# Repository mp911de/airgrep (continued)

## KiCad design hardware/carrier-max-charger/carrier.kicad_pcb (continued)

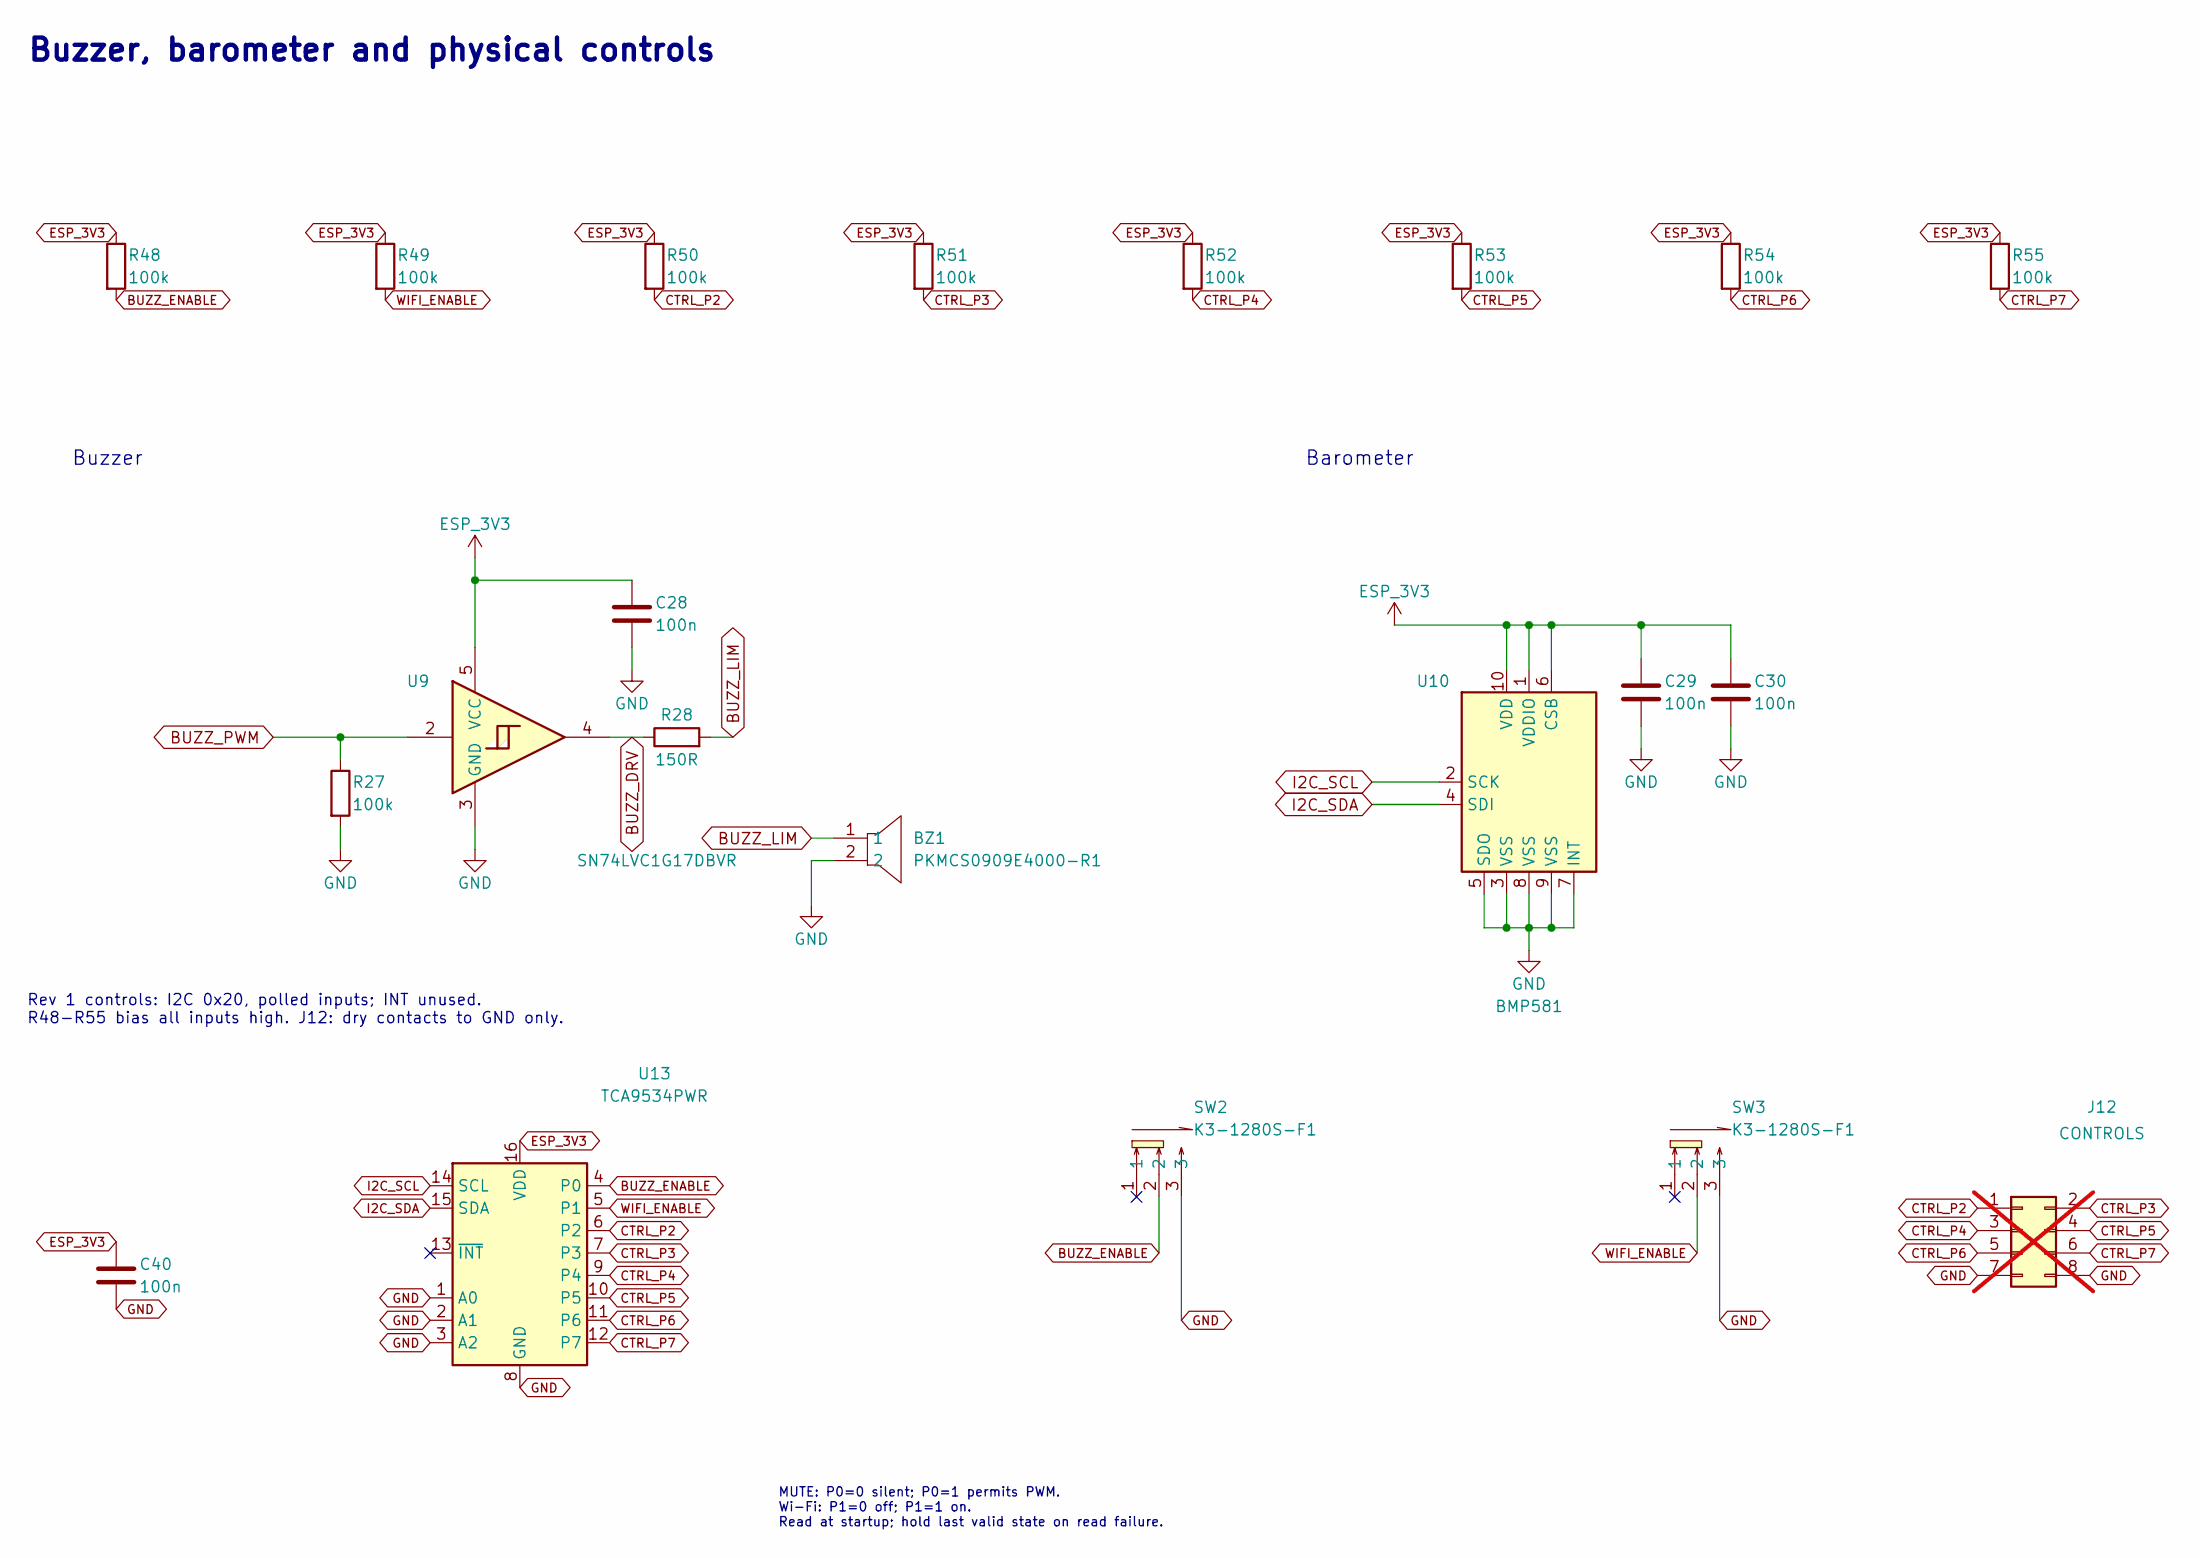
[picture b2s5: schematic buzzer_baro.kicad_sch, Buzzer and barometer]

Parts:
BZ1: PKMCS0909E4000-R1; BUZ-SMD_L9.0-W9.0_PKMCS0909E4000-R1; LCSC C910763
C28, C29, C30, C40: 100n; C_0603_1608Metric; LCSC C14663
J12: CONTROLS; PinHeader_2x04_P2.54mm_Vertical; not fitted
R27, R48, R49, R50, R51, R52, R53, R54, R55: 100k; R_0603_1608Metric; LCSC C25803
R28: 150R; R_0603_1608Metric; LCSC C22808
SW2, SW3: K3-1280S-F1; SW-SMD_K3-1280S-F1; LCSC C92658
U9: SN74LVC1G17DBVR; SOT-23-5; LCSC C7836
U10: BMP581; LGA-10_L2.0-W2.0-P0.50-TL_BMP581; MPN BMP581; LCSC C5362283
U13: TCA9534PWR; TSSOP-16_4.4x5mm_P0.65mm; LCSC C783615

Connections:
BUZZ_DRV: R28.1, U9.4
BUZZ_ENABLE: R48.2, SW2.2, U13.4 (P0)
BUZZ_LIM: BZ1.1, R28.2
BUZZ_PWM: R27.1, U9.2; also elsewhere on the board
CTRL_P2: J12.1, R50.2, U13.6 (P2)
CTRL_P3: J12.2, R51.2, U13.7 (P3)
CTRL_P4: J12.3, R52.2, U13.9 (P4)
CTRL_P5: J12.4, R53.2, U13.10 (P5)
CTRL_P6: J12.5, R54.2, U13.11 (P6)
CTRL_P7: J12.6, R55.2, U13.12 (P7)
ESP_3V3: C28.1, C29.1, C30.1, C40.1, R48.1, R49.1, R50.1, R51.1, R52.1, R53.1, R54.1, R55.1, U9.5 (VCC), U10.1 (VDDIO), U10.6 (CSB), U10.10 (VDD), U13.16 (VDD); also elsewhere on the board
GND: BZ1.2, C28.2, C29.2, C30.2, C40.2, J12.7, J12.8, R27.2, SW2.3, SW3.3, U9.3 (GND), U10.3 (VSS), U10.5 (SDO), U10.7 (INT), U10.8 (VSS), U10.9 (VSS), U13.1 (A0), U13.2 (A1), U13.3 (A2), U13.8 (GND); also elsewhere on the board
I2C_SCL: U10.2 (SCK), U13.14 (SCL); also elsewhere on the board
I2C_SDA: U10.4 (SDI), U13.15 (SDA); also elsewhere on the board
WIFI_ENABLE: R49.2, SW3.2, U13.5 (P1)

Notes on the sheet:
Barometer
MUTE: P0=0 silent; P0=1 permits PWM. Wi-Fi: P1=0 off; P1=1 on. Read at startup; hold last valid state on read failure.
Buzzer, barometer and physical controls
Buzzer
Rev 1 controls: I2C 0x20, polled inputs; INT unused. R48-R55 bias all inputs high. J12: dry contacts to GND only.

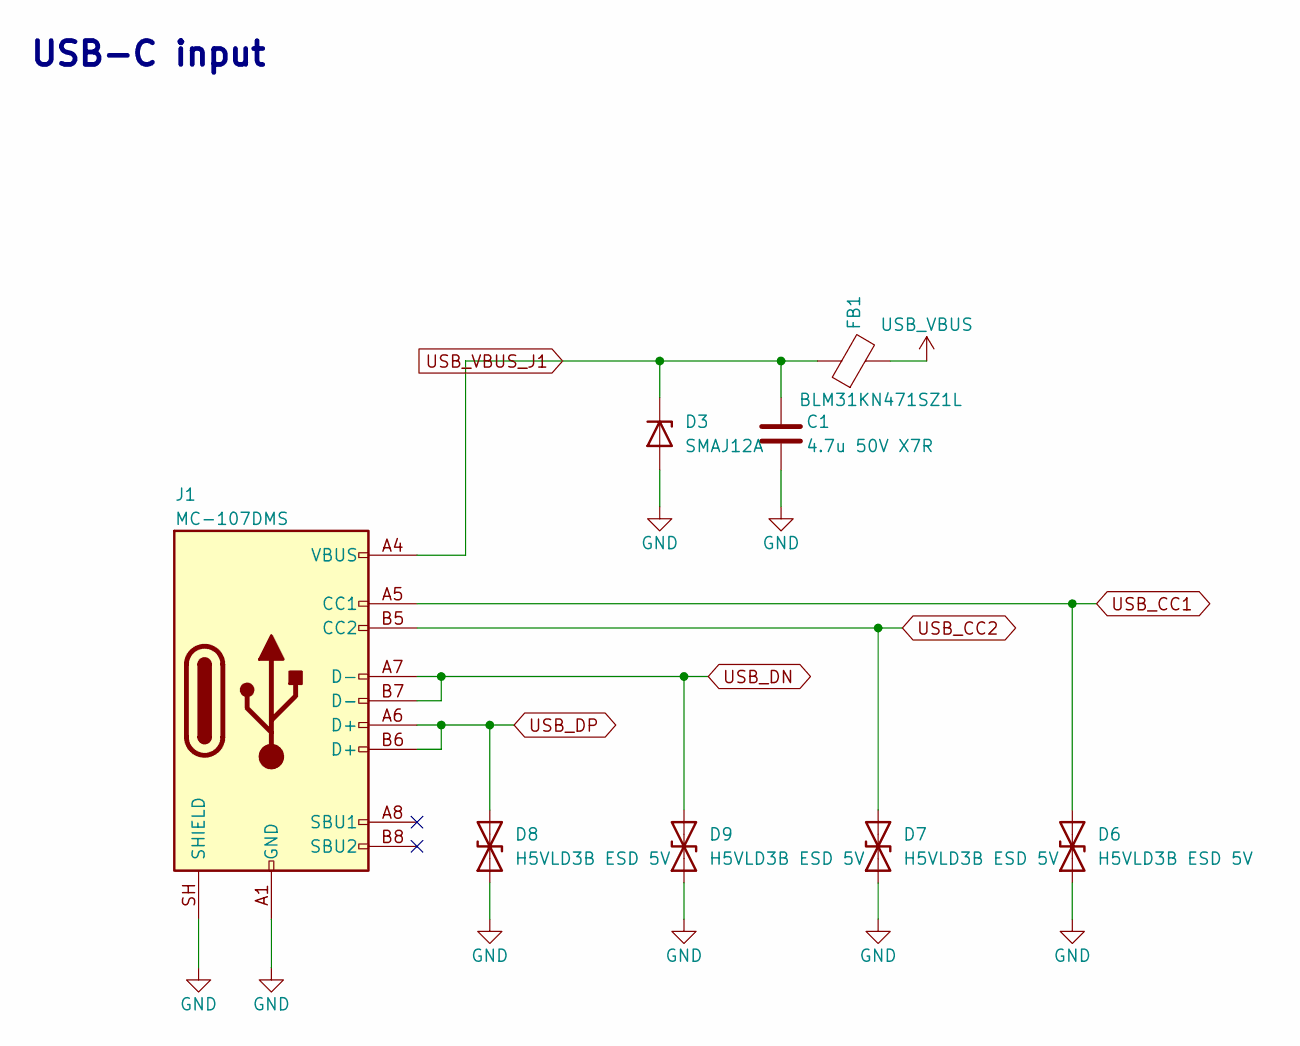
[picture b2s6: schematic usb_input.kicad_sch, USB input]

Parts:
C1: 4.7u 50V X7R; C_0805_2012Metric; LCSC C437557
D3: SMAJ12A; D_SMA; LCSC C19077531
D6, D7, D8, D9: H5VLD3B ESD 5V; D_SOD-323; MPN H5VLD3B; LCSC C20615805
FB1: BLM31KN471SZ1L; L_1206_3216Metric; LCSC C710518
J1: MC-107DMS; USB_C_Receptacle_Hanbo_MC-107DMS; LCSC C3039295

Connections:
GND: C1.2, D3.2 (A), D6.1 (A1), D7.1 (A1), D8.1 (A1), D9.1 (A1), J1.A1 (GND), J1.A12 (GND), J1.B1 (GND), J1.B12 (GND), J1.SH (SHIELD); also elsewhere on the board
USB_CC1: D6.2 (A2), J1.A5 (CC1); also elsewhere on the board
USB_CC2: D7.2 (A2), J1.B5 (CC2); also elsewhere on the board
USB_DN: D9.2 (A2), J1.A7 (D-), J1.B7 (D-); also elsewhere on the board
USB_DP: D8.2 (A2), J1.A6 (D+), J1.B6 (D+); also elsewhere on the board
USB_VBUS: FB1.2; also elsewhere on the board
USB_VBUS_J1: C1.1, D3.1 (K), FB1.1, J1.A4 (VBUS), J1.A9 (VBUS), J1.B4 (VBUS), J1.B9 (VBUS)

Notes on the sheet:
USB-C input

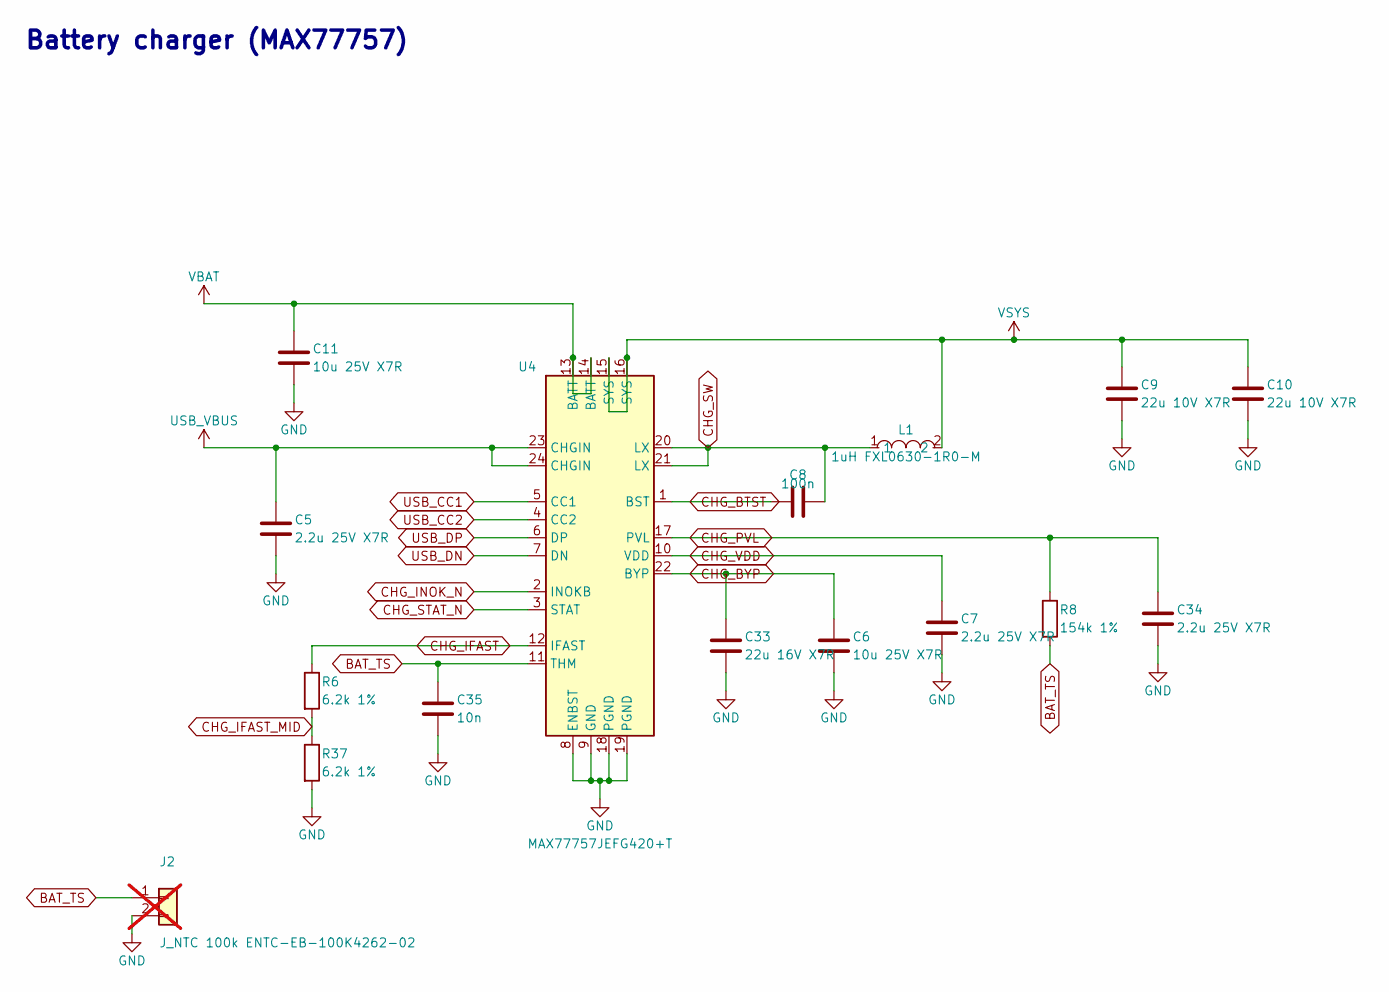
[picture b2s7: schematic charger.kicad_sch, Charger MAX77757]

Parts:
C5, C7, C34: 2.2u 25V X7R; C_0603_1608Metric; LCSC C415535
C6, C11: 10u 25V X7R; C_0805_2012Metric; LCSC C3039694
C8: 100n; C_0603_1608Metric; LCSC C14663
C9, C10: 22u 10V X7R; C_0805_2012Metric; LCSC C907991
C33: 22u 16V X7R; C_1206_3216Metric; LCSC C385906
C35: 10n; C_0603_1608Metric; LCSC C57112
J2: J_NTC 100k ENTC-EB-100K4262-02; JST_PH_B2B-PH-K_1x02_P2.00mm_Vertical_R10; not fitted
L1: 1uH FXL0630-1R0-M; IND-SMD_L7.0-W6.6_FXL0630; LCSC C167216
R6, R37: 6.2k 1%; R_0603_1608Metric; LCSC C4260
R8: 154k 1%; R_0603_1608Metric; LCSC C22881
U4: MAX77757JEFG420+T; FC2QFN-24_L3.0-W3.0-P0.40_MAX77757; LCSC C7454852

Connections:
BAT_TS: C35.1, J2.1, R8.2, U4.11 (THM); also elsewhere on the board
CHG_BTST: C8.1, U4.1 (BST)
CHG_BYP: C6.1, C33.1, U4.22 (BYP)
CHG_IFAST: R6.1, U4.12 (IFAST)
CHG_IFAST_MID: R6.2, R37.1
CHG_INOK_N: U4.2 (INOKB); also elsewhere on the board
CHG_PVL: C34.1, R8.1, U4.17 (PVL)
CHG_STAT_N: U4.3 (STAT); also elsewhere on the board
CHG_SW: C8.2, L1.1, U4.20 (LX), U4.21 (LX)
CHG_VDD: C7.1, U4.10 (VDD)
GND: C5.2, C6.2, C7.2, C9.2, C10.2, C11.2, C33.2, C34.2, C35.2, J2.2, R37.2, U4.8 (ENBST), U4.9 (GND), U4.18 (PGND), U4.19 (PGND); also elsewhere on the board
USB_CC1: U4.5 (CC1); also elsewhere on the board
USB_CC2: U4.4 (CC2); also elsewhere on the board
USB_DN: U4.7 (DN); also elsewhere on the board
USB_DP: U4.6 (DP); also elsewhere on the board
USB_VBUS: C5.1, U4.23 (CHGIN), U4.24 (CHGIN); also elsewhere on the board
VBAT: C11.1, U4.13 (BATT), U4.14 (BATT); also elsewhere on the board
VSYS: C9.1, C10.1, L1.2, U4.15 (SYS), U4.16 (SYS); also elsewhere on the board

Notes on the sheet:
Battery charger (MAX77757)

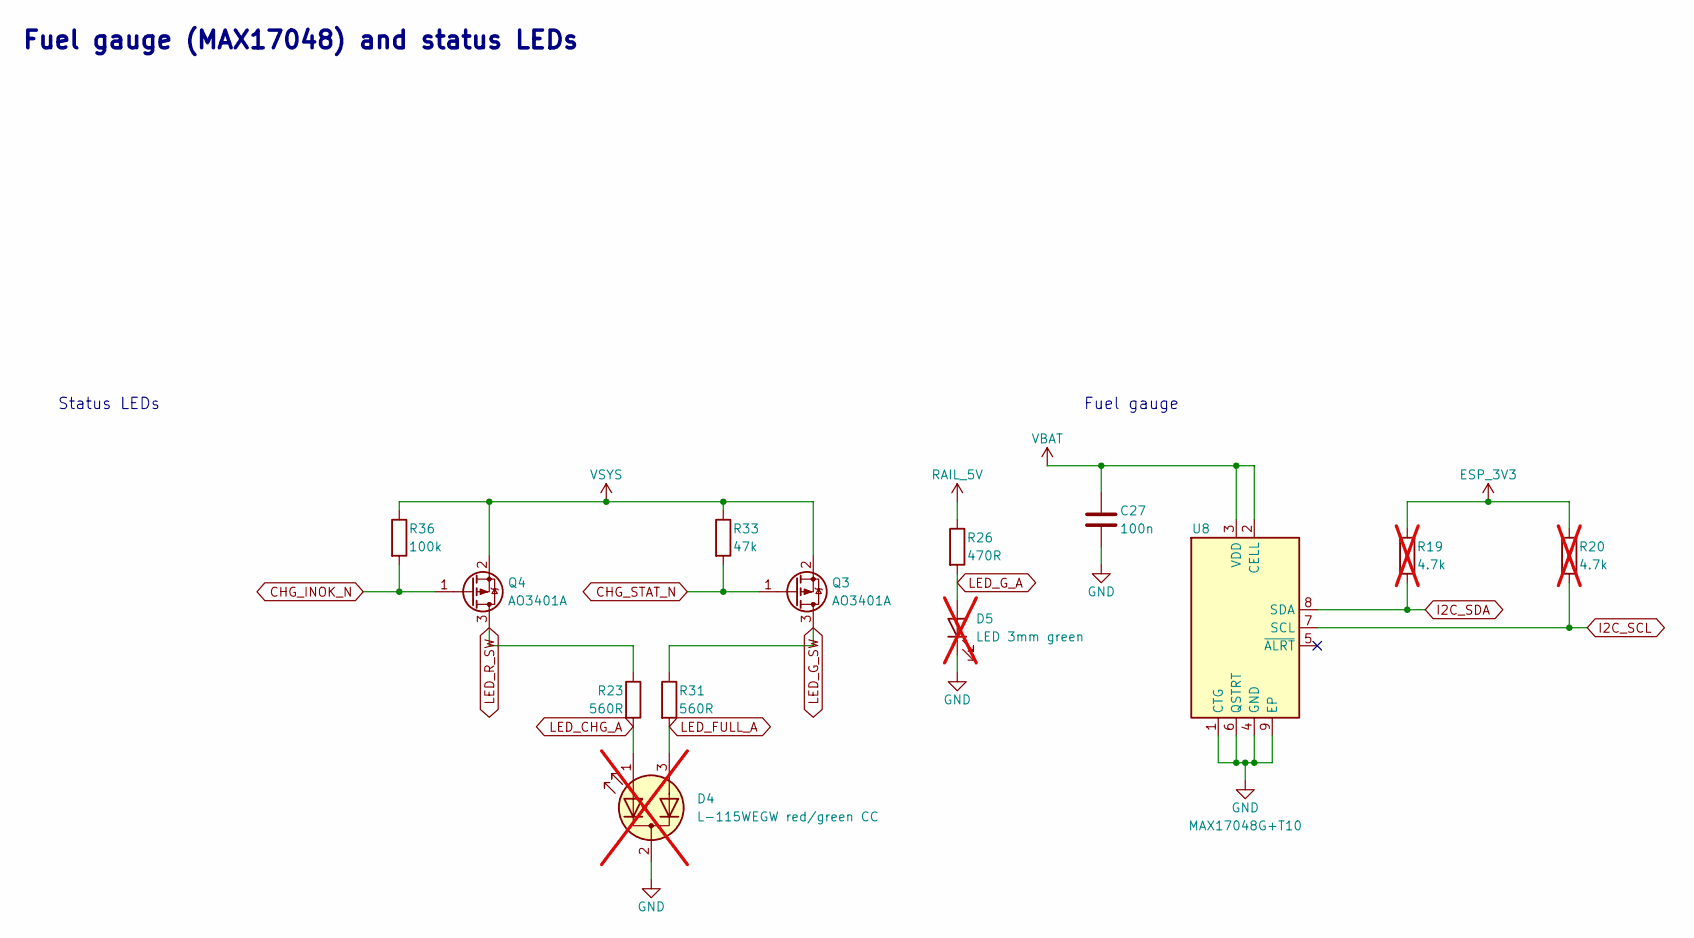
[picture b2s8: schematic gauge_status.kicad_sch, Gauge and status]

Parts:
C27: 100n; C_0603_1608Metric; LCSC C14663
D4: L-115WEGW red/green CC; LED_D3.0mm-3; not fitted
D5: LED 3mm green; LED_D3.0mm; not fitted
Q3, Q4: AO3401A; SOT-23; LCSC C15127
R19, R20: 4.7k; R_0603_1608Metric; not fitted
R23, R31: 560R; R_0603_1608Metric; LCSC C23204
R26: 470R; R_0603_1608Metric; LCSC C23179
R33: 47k; R_0603_1608Metric; LCSC C25819
R36: 100k; R_0603_1608Metric; LCSC C25803
U8: MAX17048G+T10; TDFN-8_L2.0-W2.0-P0.50-EP0.8x1.38_T822; LCSC C2682616

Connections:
CHG_INOK_N: Q4.1 (G), R36.2; also elsewhere on the board
CHG_STAT_N: Q3.1 (G), R33.2; also elsewhere on the board
ESP_3V3: R19.1, R20.1; also elsewhere on the board
GND: C27.2, D4.2 (K), D5.1 (K), U8.1 (CTG), U8.4 (GND), U8.6 (QSTRT), U8.9 (EP); also elsewhere on the board
I2C_SCL: R20.2, U8.7 (SCL); also elsewhere on the board
I2C_SDA: R19.2, U8.8 (SDA); also elsewhere on the board
LED_CHG_A: D4.1 (A1), R23.2
LED_FULL_A: D4.3 (A2), R31.2
LED_G_A: D5.2 (A), R26.2
LED_G_SW: Q3.3 (D), R31.1
LED_R_SW: Q4.3 (D), R23.1
RAIL_5V: R26.1; also elsewhere on the board
VBAT: C27.1, U8.2 (CELL), U8.3 (VDD); also elsewhere on the board
VSYS: Q3.2 (S), Q4.2 (S), R33.1, R36.1; also elsewhere on the board

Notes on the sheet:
Fuel gauge
Status LEDs
Fuel gauge (MAX17048) and status LEDs

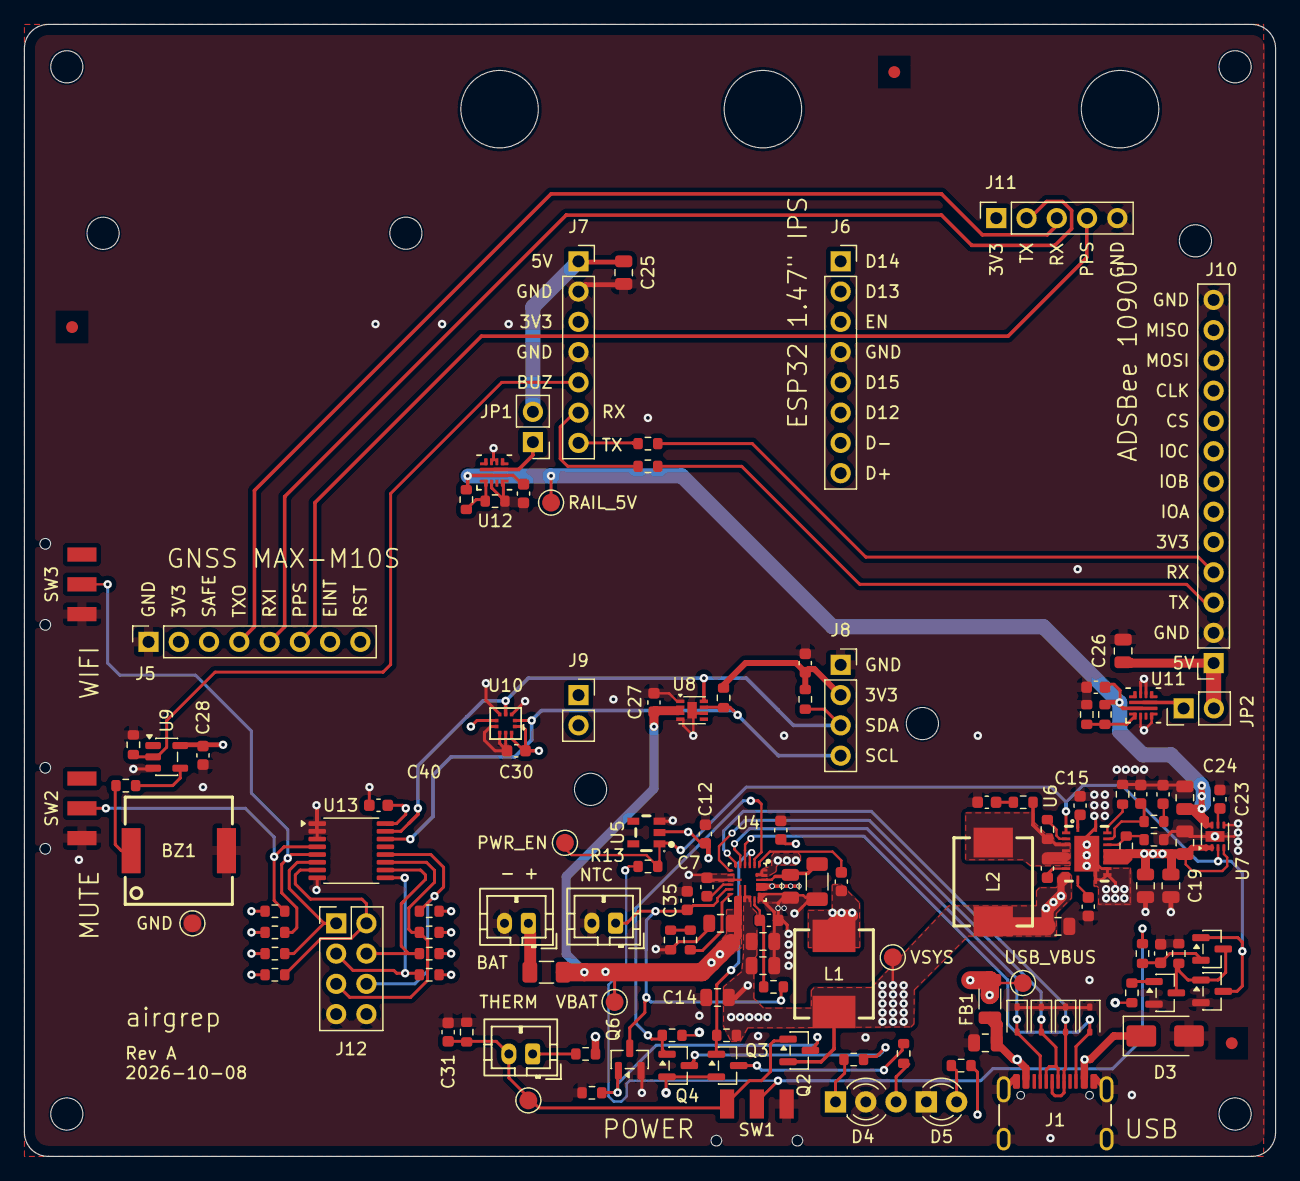
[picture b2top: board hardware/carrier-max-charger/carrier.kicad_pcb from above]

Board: 4 copper layers, 105.0 x 95.0 mm, 143 parts (0 on the bottom side), 74 nets.

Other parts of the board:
FID1, FID2, FID3: Fiducial; Fiducial_1mm_Mask2mm
MH1, MH2, MH3, MH4, MH10, MH11, MH12, MH13, MH14: MountingHole_2.7mm_M2.5
MH6, MH7, MH8: MountingHole_6.5mm

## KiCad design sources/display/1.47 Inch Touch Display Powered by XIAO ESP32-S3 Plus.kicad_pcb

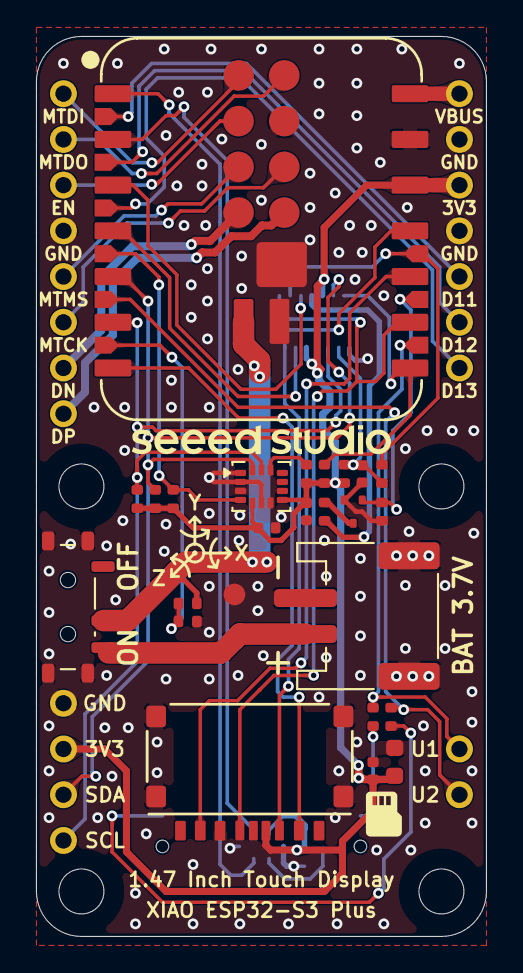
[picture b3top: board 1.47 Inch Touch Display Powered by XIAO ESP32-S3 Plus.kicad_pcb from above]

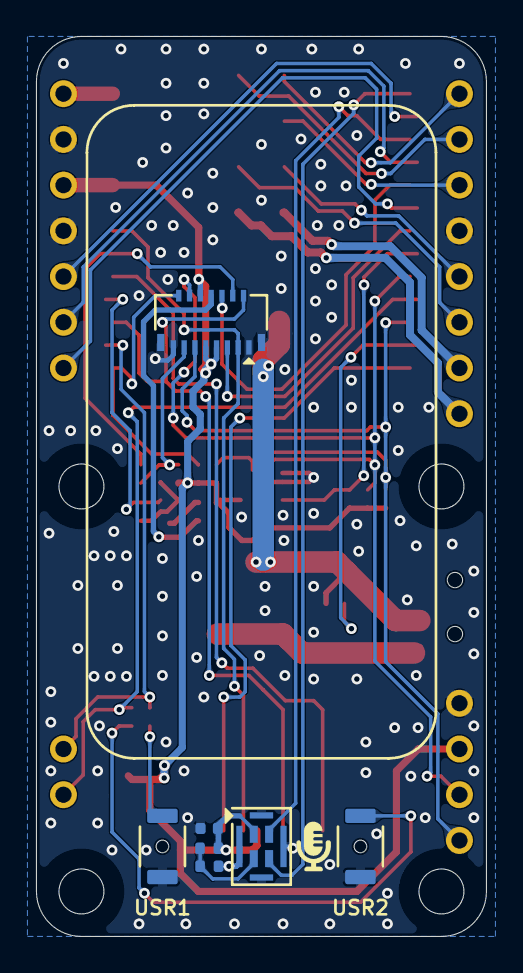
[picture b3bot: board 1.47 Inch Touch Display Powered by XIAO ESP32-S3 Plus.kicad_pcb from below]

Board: 2 copper layers, 25.0 x 50.0 mm, 58 parts (7 on the bottom side), 39 nets.

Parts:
C1: DNP/100nF; C0402
C2, C4, C5, C6: 100nF; C0402
C3: 10uF; C0603
H1, H2, H3, H4: M2.5; MountingHole_M2.5
J1: BAT CONN; WAFER-PH2.0-2P_SMD_Horizontal
J2: AFE07-S15FMA-HF; AFE07-S15FMA-HF_Pin1Right
J3: TF-123-ARP9HXX; TF-123-ARP9H15
MIC1: ZTS6131
Q1: CJ1012; SOT-523
R1: 10.5R; R0402
R2, R14: 1M; R0402
R3, R4: 5.1K; R0402
R5, R8: 1K; R0402
R6, R12, R13: 10K; R0402
R7: DNP/10K; R0402
R9, R11: 0R; R0402
R10: DNP; R0402
R15: 499K; R0402
SW1: MSK12C02; MSK12C02-HB
SW2, SW3: TS-1080S; TS-1080S-AC015XX
TP1, TP2: TestPoint_Pad_D1.2mm
TP3, TP4, TP5, TP6, TP7, TP8, TP9, TP10, TP11, TP12, TP13, TP14, TP15, TP16, TP17, TP18, TP19, TP20, TP21, TP22, TP23: TestPoint_THTPad_D1.5mm_Drill0.9mm
U1: XIAO-ESP32-S3-Plus-SMD
U2: LSM6DS3; LGA-14_3x2.5mm_P0.5mm

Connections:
3V3: C2.1, C3.1, C4.1, C5.1, C6.1, J2.7 (LCD_VDD), J2.9 (LEDA), J2.10 (TP_VDD), J3.4 (VDD), MIC1.1 (VDD), R3.1, R4.1, R6.1, R7.1, R10.1, R12.1, R13.1, TP14.1 (1_1), TP17.1 (1_1), U1.12 (3V3_OUT), U2.5 (VDDIO), U2.8 (VDD)
/03 Main/BTN_USR1: R5.2, TP22.1 (1_1), U1.21 (D19)
/03 Main/BTN_USR2: R8.2, TP23.1 (1_1), U1.19 (D15)
/03 Main/CTP_IMU_SCL: J2.11 (TP_SCL), R3.2, TP16.1 (1_1), U1.6 (D5), U2.13 (SCL)
/03 Main/CTP_IMU_SDA: J2.12 (TP_SDA), R4.2, TP15.1 (1_1), U1.5 (D4), U2.14 (SDA)
/03 Main/CTP_INT: J2.14 (TP_INT), R6.2, U1.8 (D7)
/03 Main/CTP_RST: C1.1, J2.13 (TP_RST), R7.2, R9.2
/03 Main/D11_I2S_SD: TP19.1 (1_1), U1.15 (D11)
/03 Main/D12_I2S_SCK: TP20.1 (1_1), U1.16 (D12)
/03 Main/D13_I2S_WS: TP21.1 (1_1), U1.17 (D13)
/03 Main/EN: TP5.1 (1_1), U1.26 (EN)
/03 Main/IMU_CS: R13.2, U2.12 (CS)
/03 Main/IMU_INT: R12.2, U1.18 (D14), U2.4 (INT1)
/03 Main/LCD_BL_PWM: Q1.1 (G), R2.1, U1.22 (D18)
/03 Main/LCD_CS: J2.6 (LCD_CS), U1.3 (D2)
/03 Main/LCD_DC: J2.5 (LCD_DC), U1.4 (D3)
/03 Main/LCD_RST: J2.4 (LCD_RST), R9.1, U1.23 (D17)
/03 Main/LCD_SD_MOSI: J2.3 (LCD_MOSI), J3.3 (CMD), U1.11 (D10)
/03 Main/LCD_SD_SCK: J2.2 (LCD_SCK), J3.5 (CLK), U1.9 (D8)
/03 Main/LEDK: J2.8 (LEDK), R1.1
/03 Main/MTCK: TP8.1 (1_1), U1.29 (D12/MTCK)
/03 Main/MTDI: TP3.1 (1_1), U1.24 (D14/MTDI)
/03 Main/MTDO: TP4.1 (1_1), U1.25 (D13/MTDO)
/03 Main/MTMS: TP7.1 (1_1), U1.28 (D15/MTMS)
/03 Main/PDM_CLK: MIC1.3 (CLOCK), U1.1 (D0)
/03 Main/PDM_DATA: MIC1.4 (DATA), U1.2 (D1)
/03 Main/SD_CS: J3.2 (DAT3/CD), U1.7 (D6)
/03 Main/SD_MISO: J3.7 (DAT0), U1.10 (D9)
/03 Main/USB_DN: TP9.1 (1_1), U1.30 (USB_DN)
/03 Main/USB_DP: TP10.1 (1_1), U1.31 (USB_DP)
/03 Main/VBAT_ADC: R14.2, R15.2, U1.20 (D16)
GND: C1.2, C2.2, C3.2, C4.2, C5.2, C6.2, J1.2, J1.MP1, J1.MP2, J2.1 (GND), J2.15 (GND), J2.MP1, J2.MP2, J3.6 (VSS), J3.S1, J3.S2, J3.S3, J3.S4, MIC1.5 (GND), MIC1.6 (GND), MIC1.7 (GND), MIC1.8 (GND), Q1.2 (S), R2.2, R11.2, R15.1, SW1.S1, SW1.S2, SW1.S3, SW1.S4, SW2.1, SW3.1, TP2.1 (1_1), TP6.1 (1_1), TP12.1 (1_1), TP13.1 (1_1), TP18.1 (1_1), U1.13 (GND), U1.27 (GND), U1.33 (GND), U1.34 (PAD), U2.1 (SDO/SA0), U2.2 (SDX), U2.3 (SCX), U2.6 (GND), U2.7 (GND)
unnamed: MIC1.2 (SEL), R10.2, R11.1
unnamed: Q1.3 (D), R1.2
unnamed: R5.1, SW2.2
unnamed: R8.1, SW3.2
VBAT: R14.1, SW1.2 (B), U1.32 (VBAT)
VBAT_EXT: J1.1, SW1.3 (C), TP1.1 (1_1)
VBUS: TP11.1 (1_1), U1.14 (VBUS)

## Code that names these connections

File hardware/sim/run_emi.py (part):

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    ("I2C_SCL", T_U13, 1e5, 3.3, 0.0, 60e-12, "100 kHz clock; falling edge by the driver, rise 5.1 kΩ x bus"),
    ("I2C_SDA", T_U13, 5e4, 3.3, 0.0, 60e-12, "data, half the clock edges"),
    ("ESP_UART_TX", T_ESP, 115200 / 2, 3.3, 0.0, 0.0, "display TX to R30, 115200 baud"),
    ("ADS_COMMS_RX", T_ESP, 115200 / 2, 3.3, 1e3, C_PIN, "behind R30 1 kΩ to the ADSBee"),
    ("ADS_COMMS_TX", T_RP, 115200 / 2, 3.3, 0.0, 0.0, "ADSBee TX to R29, 115200 baud"),
    ("ESP_UART_RX", T_RP, 115200 / 2, 3.3, 1e3, C_PIN, "behind R29 1 kΩ to the display"),
    ("GNSS_TXO", T_GNSS, 38400 / 2, 3.3, 0.0, C_PIN, "GNSS TX, 38400 baud"),
    ("GNSS_RXI", T_RP, 38400 / 2, 3.3, 0.0, C_PIN, "ADSBee TX to the GNSS"),
    ("GNSS_PPS", T_GNSS, 2.0, 3.3, 0.0, C_PIN, "1 Hz pulse"),
    ("BUZZ_PWM", T_ESP, 8e3, 3.3, 0.0, C_PIN, "4 kHz buzzer PWM to U9"),
    ("BUZZ_DRV", T_U9, 8e3, 3.3, 0.0, 0.0, "U9 output to R28"),
)
NOT_MODELLED = ("USB_DP and USB_DN carry only the BC1.2 detection at plug-in, no traffic. "
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
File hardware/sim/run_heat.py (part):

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# --- Contacts and passives: (nominal, high). Nominal is an estimate, high is the data sheet maximum
USB_CONTACT = (0.020, 0.040)  # Hanbo MC-107DMS: 40 mΩ max per contact; 4 VBUS + 4 GND contacts
FB_R = (0.015, 0.020)  # FB1 BLM31KN471SZ1L: 20 mΩ max DCR (LCSC C710518); nominal estimated
USB_J1 = "USB_VBUS_J1"  # USB connector VBUS pins, D1 and C1, ahead of FB1
JST_CONTACT = (0.005, 0.010)  # JST PH: 10 mΩ max initial per contact
SOCKET_CONTACT = (0.010, 0.020)  # 2.54 mm pin socket or shunt contact (estimate, no data sheet on file)
FUSE_R = (0.011, 0.015)  # F1 Littelfuse 0466005.NRHF 5 A (C57525): 11 mΩ nominal cold; high adds self-heating
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            track("USB_VBUS", {("FB1", ("2",)): i_in, ("U4", u4["vin"]): -i_in})
            track(CHG_NETS["sw"], {("U4", u4["sw"]): i_l1, ("L1", ("1",)): -i_l1}, "CHG_SW")
            if CHG["inductor_on_vsys"]:
                # MAX77757: L1 feeds the VSYS copper, the SYS pins take the charge current into the BATFET
                inj = {("L1", ("2",)): i_l1, ("U4", u4["sys"]): -i_chg}
                if b["iin"]:
                    inj[("L2", None)] = -(i_l1 - i_chg)
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        rep.add()
    rep.table(["Path", "Resistance"], [[k, "%.1f mΩ" % (v * 1e3) + (" (assumed)" if key in nominal.unrouted else "")]
                                       for key, k, v in (
        ("USB_VBUS input", f"USB_VBUS_J1: {CONN['usb']} VBUS pins to FB1", r_net["USB_VBUS input"]),
        ("USB_VBUS", "USB_VBUS: FB1 to U4 %s" % pin["vin"], r_net["USB_VBUS"]),
        ("CHG_SW", "%s: U4 %s to L1" % (CHG_NETS["sw"], pin["sw"]), r_net["CHG_SW"]),
        ("VSYS L1", "%s: L1 to U4 %s" % (CHG_NETS["sw2"] or "VSYS", "SW2" if CHG_NETS["sw2"] else pin["sys"]), r_net["VSYS L1"]),
        ("VSYS", "VSYS: U4 %s to L2" % pin["sys"], r_net["VSYS"]),
        ("VBAT", "VBAT + CHG_BAT: F1 through Q13 to U4 BAT (copper only)" if CHG.get("ship_fet") else "VBAT: F1 to U4 %s" % pin["bat"], r_net["VBAT"]),
        ("BAT_IN", f"BAT_IN: {CONN['battery']} to F1", r_net["BAT_IN"]),
        ("BOOST_SW", "BOOST_SW: L2 to U6 SW", r_net["BOOST_SW"]),
        ("BOOST_5V", "BOOST_5V: U6 VOUT to U7 VIN", r_net["BOOST_5V"]),
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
